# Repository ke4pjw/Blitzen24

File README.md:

# Introduction
The Blitzen 24 is a 24-port pixel controller for E1.31 (sACN) and DDP, built on the Parallax Propeller 2 (P2).

# Current State
The current release is **Blitzen 24 Edge 2.6.6 (Rocklin)**. What changed in each release is in [CHANGELOG.md](CHANGELOG.md).

Evaluation boards are available. Please contact me at ttrapp at ieee dot org if you would like to purchase one.

# Features
- **24 WS2811/WS2812 pixel outputs**, with per-output color order and brightness.
- **4 extra outputs (25–28)** for either quad DMX or a long-range pixel board.
- **E1.31 (sACN) or DDP input**, selectable per controller. Each protocol keeps its own saved layout, so you can switch back and forth without losing either one.
- **W6100 Ethernet**, with DHCP or a static address, DNS, and mDNS (`<hostname>.local`).
- **Web configuration**: network, outputs, inputs, DMX and saved configs. Live input stats, and a banner when changes haven't been saved.
- **Online upgrades** from the configs page, with a choice of the release or development channel. Each file shows download progress and is checked against its MD5.
- **OLED and rotary encoder**, with these screens: Stats, a QR code for the controller's web page, Network, Version, and Pixel Test.
- **Pixel tests**: Red, Green, Blue, White and Rainbow on each port. Start them from the OLED or the web Outputs page.

# Getting It
- **Source with Boards:** [https://griswoldfx.visualstudio.com/_git/Blitzen 24](https://griswoldfx.visualstudio.com/_git/Blitzen%2024). Each release has a branch named `Blitzen_24_Edge_<version>_<name>`.
- **Source code only in Github:** [https://github.com/ke4pjw/Blitzen24](https://github.com/ke4pjw/Blitzen24), a mirror of this repo.
- **Binary Distribution:** [https://filesgriswoldfxcom.blob.core.windows.net/firmware/Blitzen24/Blitzen 24 Edge 2.6.6 (Rocklin).zip](https://filesgriswoldfxcom.blob.core.windows.net/firmware/Blitzen24/Blitzen%2024%20Edge%202.6.6%20(Rocklin).zip). It holds everything that goes on the SD card.
- **Updates thread:** [Parallax Forums](https://forums.parallax.com/discussion/174560/blitzen-24-e1-31-pixel-light-controller-updates-thread/)

As always, you can update directly from the controller itself on the configs page.

# Repository Layout
| Path | Contents |
|------|----------|
| `Blitzen24.spin2` | Top-level firmware: web server, configuration, OLED menus |
| `W6100drv.spin2` | W6100 Ethernet driver and the fast E1.31/DDP receive cog |
| `pixeltest.spin2` | Pixel test patterns, which run in their own cog |
| `tt_rgbx_pixel.spin2`, `tt_dmx_tx.spin2` | Pixel and DMX output drivers |
| `micro_sd_fat32_fs_v180.spin2` | SD card / FAT32 filesystem driver |
| `SDCARD/` | Web pages and other files that go on the SD card |
| `Hardware/` | KiCad schematics and board layout |
| `MemoryStructure.md` | Hub memory and config layout |
| `CHANGELOG.md` | Release history |

# Known Bugs
- [#67](https://griswoldfx.visualstudio.com/Blitzen%2024/_workitems/edit/67/) In DDP mode, the pixel buffer is too small for 24 outputs × 1,020 pixels plus DMX.
- [#76](https://griswoldfx.visualstudio.com/Blitzen%2024/_workitems/edit/76/) E1.31 DMX universes copy only 510 of 512 channels.

# To Do
- [#58](https://griswoldfx.visualstudio.com/Blitzen%2024/_workitems/edit/58/) NTP client.
- [#68](https://griswoldfx.visualstudio.com/Blitzen%2024/_workitems/edit/68/), [#69](https://griswoldfx.visualstudio.com/Blitzen%2024/_workitems/edit/69/), [#70](https://griswoldfx.visualstudio.com/Blitzen%2024/_workitems/edit/70/) Configure the Blitzen 24 from xLights: discovery, a JSON config API, and an xLights driver.

# Build
Releases are built with the Spin Tools compiler (`spinc`, 0.57.3):

```
spinc -u -b -o _BOOT_P2 Blitzen24.spin2
```

`-u` removes unused methods and `-b` writes a binary. Copy the result to the SD card as `_BOOT_P2.BIX`, along with the files in `SDCARD/`.

# Credits
- **Stephen M. Moraco and Chris Gadd** wrote the `micro_sd_fat32_fs` SD card / FAT32 driver.
- **Rayman** wrote the cog-less SD card driver used in early releases.

# Contribute
If you wish to contribute, please email me. ttrapp at ieee dot org

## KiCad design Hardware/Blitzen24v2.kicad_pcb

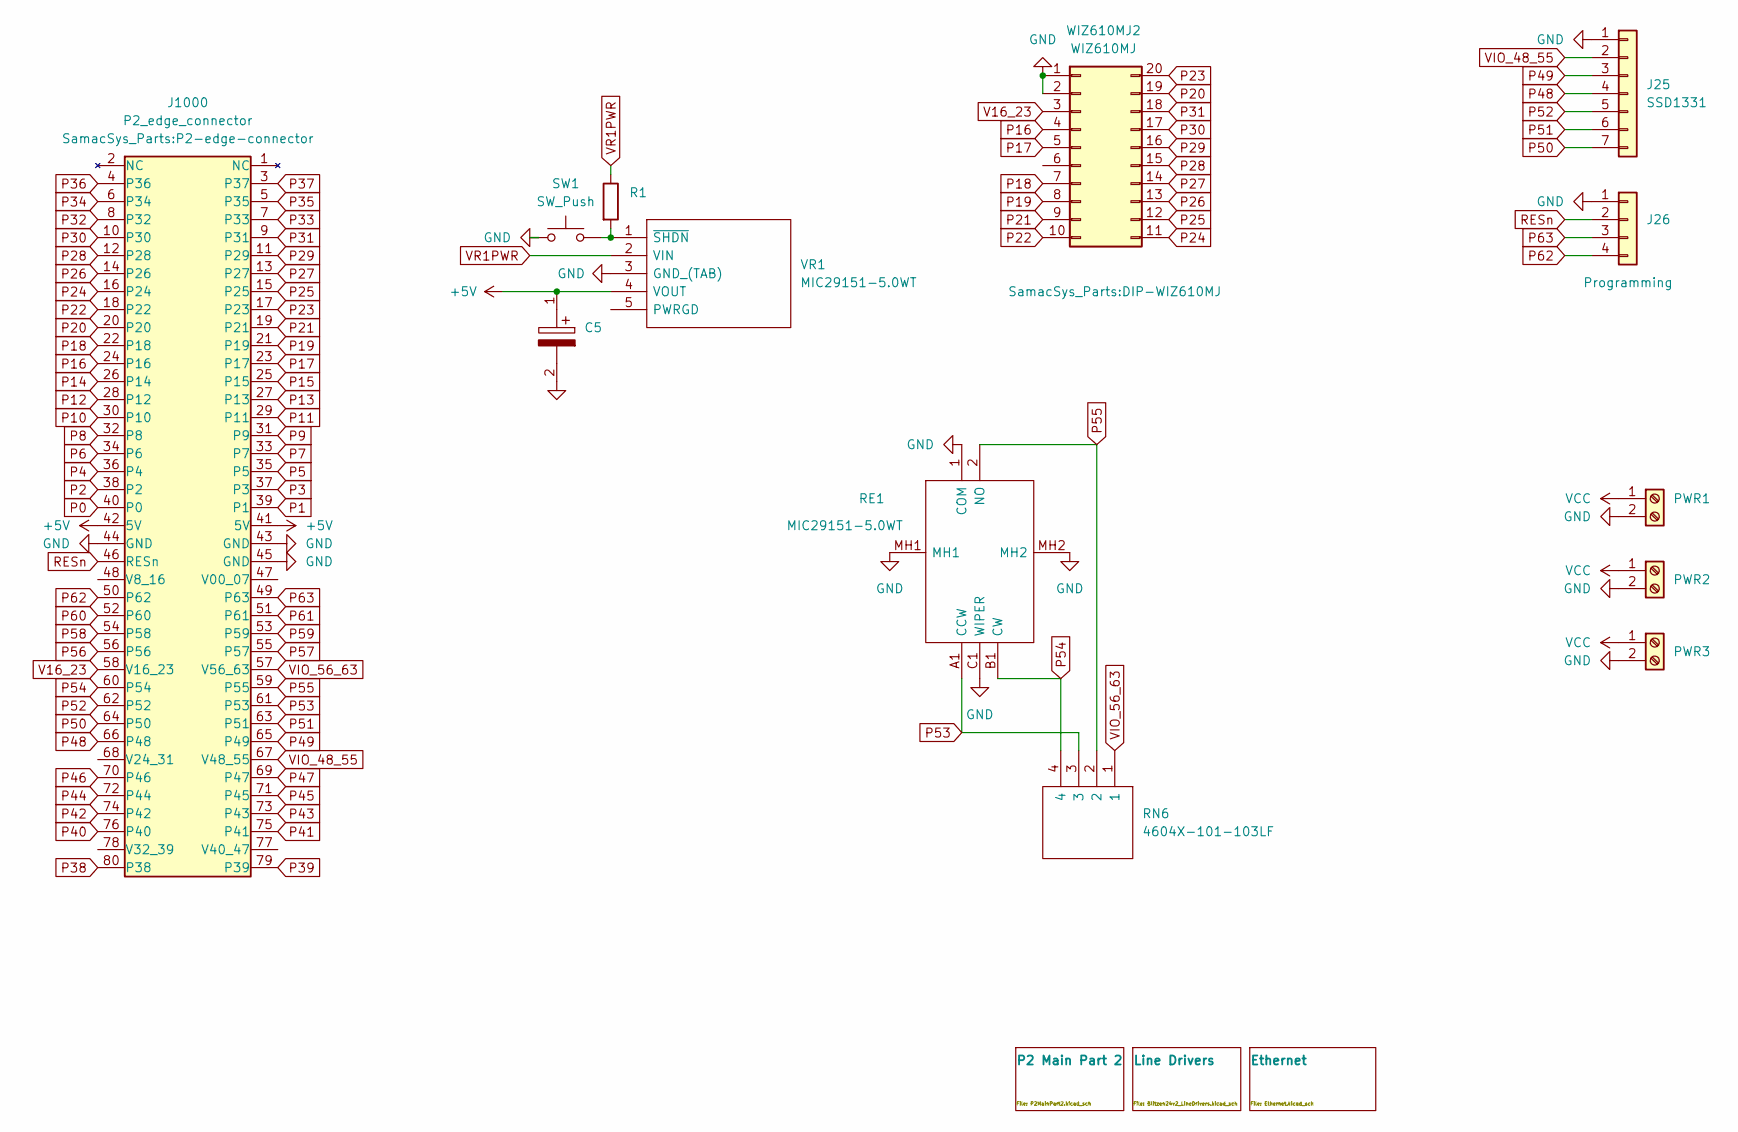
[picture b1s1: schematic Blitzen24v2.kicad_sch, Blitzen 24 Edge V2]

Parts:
C5: Mouser Part Number 80-ESS106M025AB2AA
J25: SSD1331
J26: Programming; PinHeader_1x04_P2.54mm_Vertical
J1000: P2_edge_connector; P2-edge-connector
PWR1, PWR2, PWR3: Screw_Terminal_01x02; TerminalBlock_Dinkle_DT-55-B01X-02_P10.00mm
R1: (no value)
RE1: MIC29151-5.0WT; PEC11L4015FS0020; Mouser Part Number 652-PEC11L4015FS0020
RN6: 4604X-101-103LF; 4604X101103LF; Mouser Part Number 652-4604X-1LF-10K
SW1: SW_Push
VR1: MIC29151-5.0WT; Mouser Part Number MIC29151-5.0WT
WIZ610MJ2: WIZ610MJ; DIP-WIZ610MJ

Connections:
+5V: C5.1, J1000.41 (5V), J1000.42 (5V), VR1.4 (VOUT); also elsewhere on the board
unnamed: R1.2, SW1.2, VR1.1 (~SHDN)
P0: J1000.40 (P0); also elsewhere on the board
P1: J1000.39 (P1); also elsewhere on the board
P2: J1000.38 (P2); also elsewhere on the board
P3: J1000.37 (P3); also elsewhere on the board
P4: J1000.36 (P4); also elsewhere on the board
P5: J1000.35 (P5); also elsewhere on the board
P6: J1000.34 (P6); also elsewhere on the board
P7: J1000.33 (P7); also elsewhere on the board
P8: J1000.32 (P8); also elsewhere on the board
P9: J1000.31 (P9); also elsewhere on the board
P10: J1000.30 (P10); also elsewhere on the board
P11: J1000.29 (P11); also elsewhere on the board
P12: J1000.28 (P12); also elsewhere on the board
P13: J1000.27 (P13); also elsewhere on the board
P14: J1000.26 (P14); also elsewhere on the board
P15: J1000.25 (P15); also elsewhere on the board
P16: J1000.24 (P16), WIZ610MJ2.4
P17: J1000.23 (P17), WIZ610MJ2.5
P18: J1000.22 (P18), WIZ610MJ2.7
P19: J1000.21 (P19), WIZ610MJ2.8
P20: J1000.20, WIZ610MJ2.19
P21: J1000.19 (P21), WIZ610MJ2.9
P22: J1000.18 (P22), WIZ610MJ2.10
P23: J1000.17 (P23), WIZ610MJ2.20
P24: J1000.16 (P24), WIZ610MJ2.11
P25: J1000.15 (P25), WIZ610MJ2.12
P26: J1000.14 (P26), WIZ610MJ2.13
P27: J1000.13 (P27), WIZ610MJ2.14
P28: J1000.12 (P28), WIZ610MJ2.15
P29: J1000.11 (P29), WIZ610MJ2.16
P30: J1000.10 (P30), WIZ610MJ2.17
P31: J1000.9 (P31), WIZ610MJ2.18
P32: J1000.8 (P32); also elsewhere on the board
P33: J1000.7 (P33); also elsewhere on the board
P34: J1000.6 (P34); also elsewhere on the board
P35: J1000.5 (P35); also elsewhere on the board
P36: J1000.4 (P36); also elsewhere on the board
P37: J1000.3 (P37); also elsewhere on the board
P38: J1000.80 (P38); also elsewhere on the board
P39: J1000.79 (P39); also elsewhere on the board
P40: J1000.76 (P40)
P41: J1000.75 (P41)
P42: J1000.74 (P42)
P43: J1000.73 (P43)
P44: J1000.72 (P44); also elsewhere on the board
P45: J1000.71 (P45); also elsewhere on the board
P46: J1000.70 (P46); also elsewhere on the board
P47: J1000.69 (P47); also elsewhere on the board
P48: J25.4, J1000.66 (P48)
P49: J25.3, J1000.65 (P49)
P50: J25.7, J1000.64 (P50)
P51: J25.6, J1000.63 (P51)
P52: J25.5, J1000.62 (P52)
P53: J1000.61 (P53), RE1.A1 (CCW), RN6.3
P54: J1000.60 (P54), RE1.B1 (CW), RN6.4
P55: J1000.59 (P55), RE1.2 (NO), RN6.2
P56: J1000.56
P57: J1000.55 (P57)
P58: J1000.54 (P58)
P59: J1000.53 (P59)
P60: J1000.52 (P60)
P61: J1000.51 (P61)
P62: J26.4, J1000.50 (P62)
P63: J26.3, J1000.49 (P63)
RESn: J26.2, J1000.46 (RESn)
V16_23: J1000.58 (V16_23), WIZ610MJ2.3
VCC: PWR1.1, PWR2.1, PWR3.1; also elsewhere on the board
VIO_48_55: J25.2, J1000.67 (V48_55)
VIO_56_63: J1000.57 (V56_63), RN6.1
VR1PWR: R1.1, VR1.2 (VIN); also elsewhere on the board

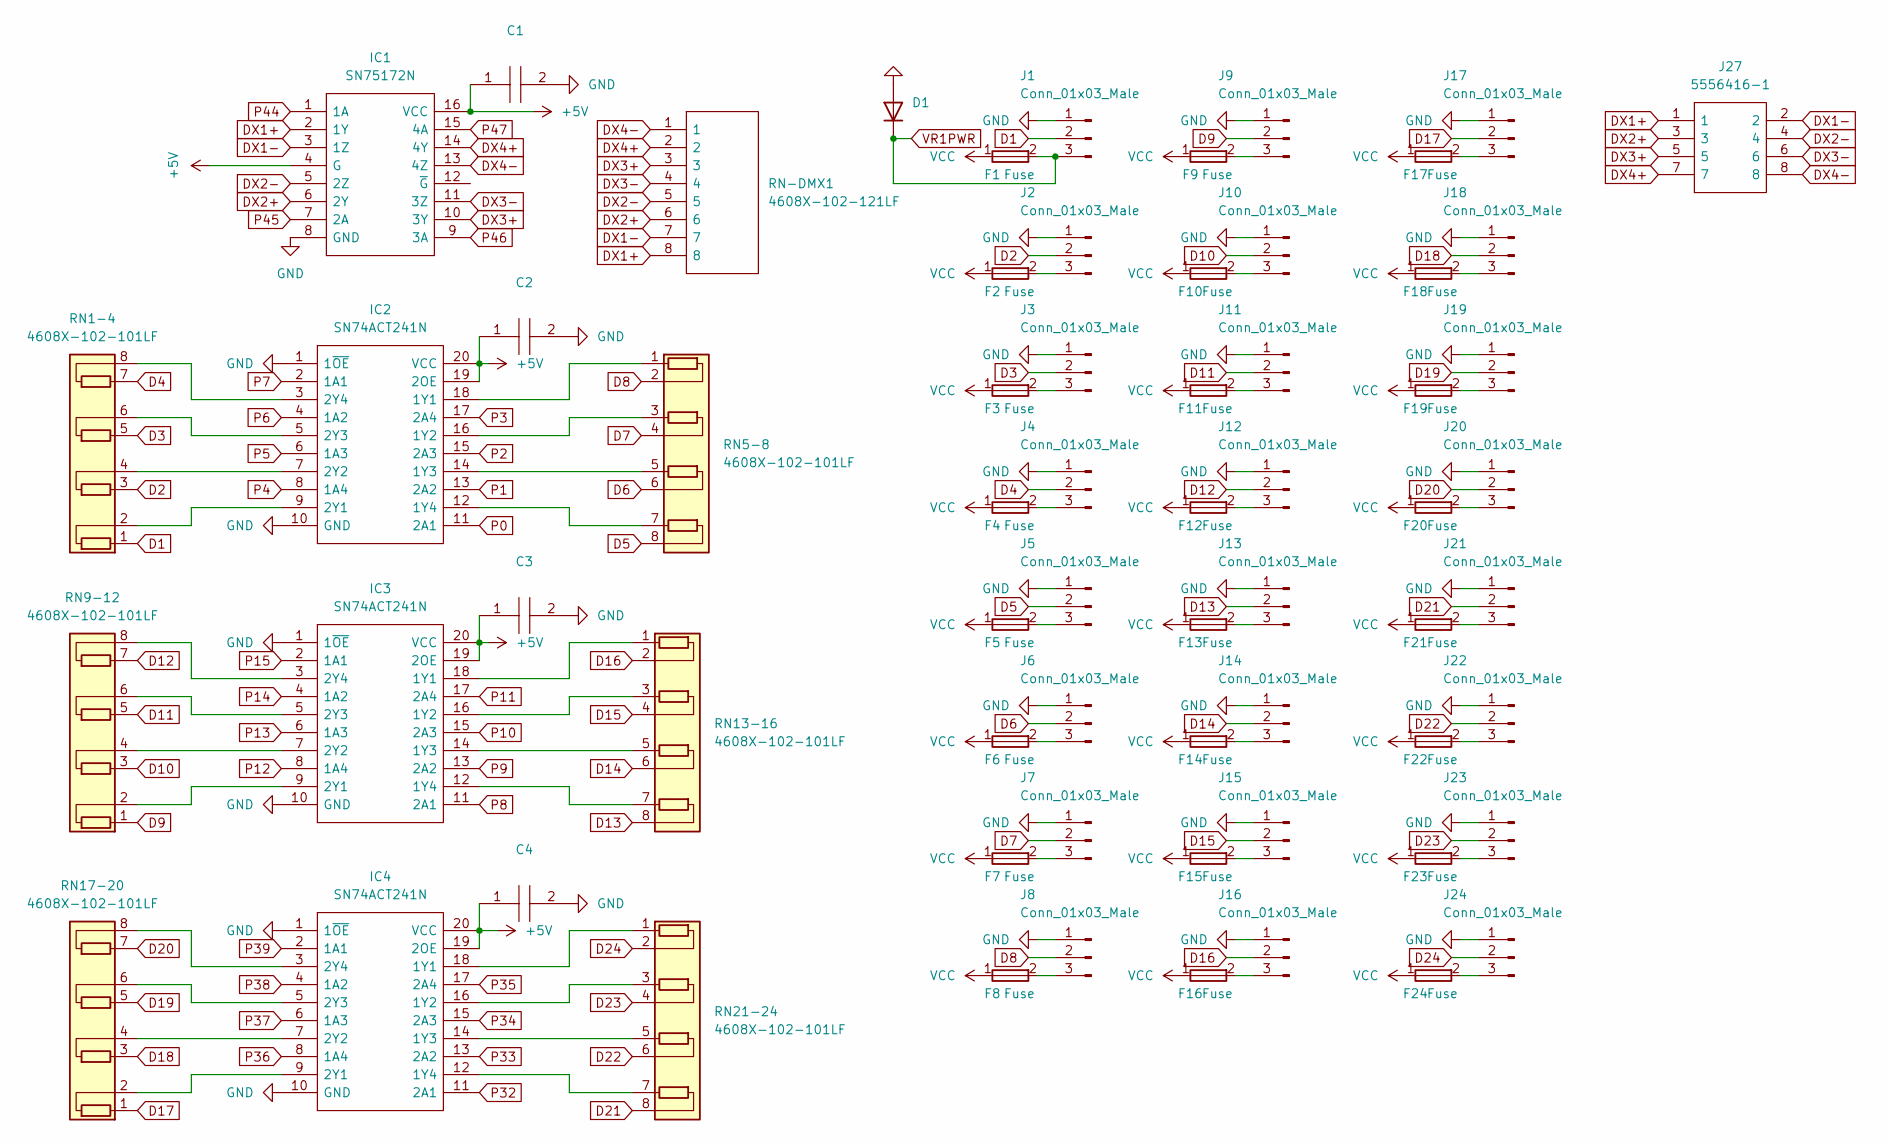
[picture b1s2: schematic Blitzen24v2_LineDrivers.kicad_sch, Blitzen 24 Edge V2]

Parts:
C1, C2, C3, C4: Mouser Part Number 80-C320C104K5R
D1: (no value)
F1, F2, F3, F4, F5, F6, F7, F8, F9, F10, F11, F12, F13, F14, F15, F16, F17, F18, F19, F20, F21, F22, F23, F24: Fuse; Fuseholder_Blade_Mini_Keystone_3568
IC1: SN75172N; DIP794W53P254L1930H508Q16N; Mouser Part Number 595-SN75172N
IC2, IC3, IC4: SN74ACT241N; DIP254P762X508-20; Mouser Part Number 595-SN74ACT241N
J1, J2, J3, J4, J5, J6, J7, J8, J9, J10, J11, J12, J13, J14, J15, J16, J17, J18, J19, J20, J21, J22, J23, J24: Conn_01x03_Male; PhoenixContact_MSTBVA_2,5_3-G-5,08_1x03_P5.08mm_Vertical
J27: 5556416-1; 55564161; Mouser Part Number 571-5556416-1
RN1-4, RN5-8, RN9-12, RN13-16, RN17-20, RN21-24: 4608X-102-101LF; R_Array_SIP8
RN-DMX1: 4608X-102-121LF; 4608X102121LF; Mouser Part Number 652-4608X-2LF-120

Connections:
+5V: C1.1, C2.1, C3.1, C4.1, IC1.4 (G), IC1.16 (VCC), IC2.19 (2OE), IC2.20 (VCC), IC3.19 (2OE), IC3.20 (VCC), IC4.19 (2OE), IC4.20 (VCC); also elsewhere on the board
D1: J1.2, RN1-4.1 (R1.1)
D2: J2.2, RN1-4.3 (R2.1)
D3: J3.2, RN1-4.5 (R3.1)
D4: J4.2, RN1-4.7 (R4.1)
D5: J5.2, RN5-8.8 (R4.2)
D6: J6.2, RN5-8.6 (R3.2)
D7: J7.2, RN5-8.4 (R2.2)
D8: J8.2, RN5-8.2 (R1.2)
D9: J9.2, RN9-12.1 (R1.1)
D10: J10.2, RN9-12.3 (R2.1)
D11: J11.2, RN9-12.5 (R3.1)
D12: J12.2, RN9-12.7 (R4.1)
D13: J13.2, RN13-16.8 (R4.2)
D14: J14.2, RN13-16.6 (R3.2)
D15: J15.2, RN13-16.4 (R2.2)
D16: J16.2, RN13-16.2 (R1.2)
D17: J17.2, RN17-20.1 (R1.1)
D18: J18.2, RN17-20.3 (R2.1)
D19: J19.2, RN17-20.5 (R3.1)
D20: J20.2, RN17-20.7 (R4.1)
D21: J21.2, RN21-24.8 (R4.2)
D22: J22.2, RN21-24.6 (R3.2)
D23: J23.2, RN21-24.4 (R2.2)
D24: J24.2, RN21-24.2 (R1.2)
DX1+: IC1.2 (1Y), J27.1, RN-DMX1.8
DX1-: IC1.3 (1Z), J27.2, RN-DMX1.7
DX2+: IC1.6 (2Y), J27.3, RN-DMX1.6
DX2-: IC1.5 (2Z), J27.4, RN-DMX1.5
DX3+: IC1.10 (3Y), J27.5, RN-DMX1.3
DX3-: IC1.11 (3Z), J27.6, RN-DMX1.4
DX4+: IC1.14 (4Y), J27.7, RN-DMX1.2
DX4-: IC1.13 (4Z), J27.8, RN-DMX1.1
unnamed: F2.2, J2.3
unnamed: F3.2, J3.3
unnamed: F4.2, J4.3
unnamed: F5.2, J5.3
unnamed: F6.2, J6.3
unnamed: F7.2, J7.3
unnamed: F8.2, J8.3
unnamed: F9.2, J9.3
unnamed: F10.2, J10.3
unnamed: F11.2, J11.3
unnamed: F12.2, J12.3
unnamed: F13.2, J13.3
unnamed: F14.2, J14.3
unnamed: F15.2, J15.3
unnamed: F16.2, J16.3
unnamed: F17.2, J17.3
unnamed: F18.2, J18.3
unnamed: F19.2, J19.3
unnamed: F20.2, J20.3
unnamed: F21.2, J21.3
unnamed: F22.2, J22.3
unnamed: F23.2, J23.3
unnamed: F24.2, J24.3
unnamed: IC2.3 (2Y4), RN1-4.8 (R4.2)
unnamed: IC2.5 (2Y3), RN1-4.6 (R3.2)
unnamed: IC2.7 (2Y2), RN1-4.4 (R2.2)
unnamed: IC2.9 (2Y1), RN1-4.2 (R1.2)
unnamed: IC2.12 (1Y4), RN5-8.7 (R4.1)
unnamed: IC2.14 (1Y3), RN5-8.5 (R3.1)
unnamed: IC2.16 (1Y2), RN5-8.3 (R2.1)
unnamed: IC2.18 (1Y1), RN5-8.1 (R1.1)
unnamed: IC3.3 (2Y4), RN9-12.8 (R4.2)
unnamed: IC3.5 (2Y3), RN9-12.6 (R3.2)
unnamed: IC3.7 (2Y2), RN9-12.4 (R2.2)
unnamed: IC3.9 (2Y1), RN9-12.2 (R1.2)
unnamed: IC3.12 (1Y4), RN13-16.7 (R4.1)
unnamed: IC3.14 (1Y3), RN13-16.5 (R3.1)
unnamed: IC3.16 (1Y2), RN13-16.3 (R2.1)
unnamed: IC3.18 (1Y1), RN13-16.1 (R1.1)
unnamed: IC4.3 (2Y4), RN17-20.8 (R4.2)
unnamed: IC4.5 (2Y3), RN17-20.6 (R3.2)
unnamed: IC4.7 (2Y2), RN17-20.4 (R2.2)
unnamed: IC4.9 (2Y1), RN17-20.2 (R1.2)
unnamed: IC4.12 (1Y4), RN21-24.7 (R4.1)
unnamed: IC4.14 (1Y3), RN21-24.5 (R3.1)
unnamed: IC4.16 (1Y2), RN21-24.3 (R2.1)
unnamed: IC4.18 (1Y1), RN21-24.1 (R1.1)
P0: IC2.11 (2A1); also elsewhere on the board
P1: IC2.13 (2A2); also elsewhere on the board
P2: IC2.15 (2A3); also elsewhere on the board
P3: IC2.17 (2A4); also elsewhere on the board
P4: IC2.8 (1A4); also elsewhere on the board
P5: IC2.6 (1A3); also elsewhere on the board
P6: IC2.4 (1A2); also elsewhere on the board
P7: IC2.2 (1A1); also elsewhere on the board
P8: IC3.11 (2A1); also elsewhere on the board
P9: IC3.13 (2A2); also elsewhere on the board
P10: IC3.15 (2A3); also elsewhere on the board
P11: IC3.17 (2A4); also elsewhere on the board
P12: IC3.8 (1A4); also elsewhere on the board
P13: IC3.6 (1A3); also elsewhere on the board
P14: IC3.4 (1A2); also elsewhere on the board
P15: IC3.2 (1A1); also elsewhere on the board
P32: IC4.11 (2A1); also elsewhere on the board
P33: IC4.13 (2A2); also elsewhere on the board
P34: IC4.15 (2A3); also elsewhere on the board
P35: IC4.17 (2A4); also elsewhere on the board
P36: IC4.8 (1A4); also elsewhere on the board
P37: IC4.6 (1A3); also elsewhere on the board
P38: IC4.4 (1A2); also elsewhere on the board
P39: IC4.2 (1A1); also elsewhere on the board
P44: IC1.1 (1A); also elsewhere on the board
P45: IC1.7 (2A); also elsewhere on the board
P46: IC1.9 (3A); also elsewhere on the board
P47: IC1.15 (4A); also elsewhere on the board
VCC: F1.1, F2.1, F3.1, F4.1, F5.1, F6.1, F7.1, F8.1, F9.1, F10.1, F11.1, F12.1, F13.1, F14.1, F15.1, F16.1, F17.1, F18.1, F19.1, F20.1, F21.1, F22.1, F23.1, F24.1; also elsewhere on the board
VR1PWR: D1.1 (K), F1.2, J1.3; also elsewhere on the board

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
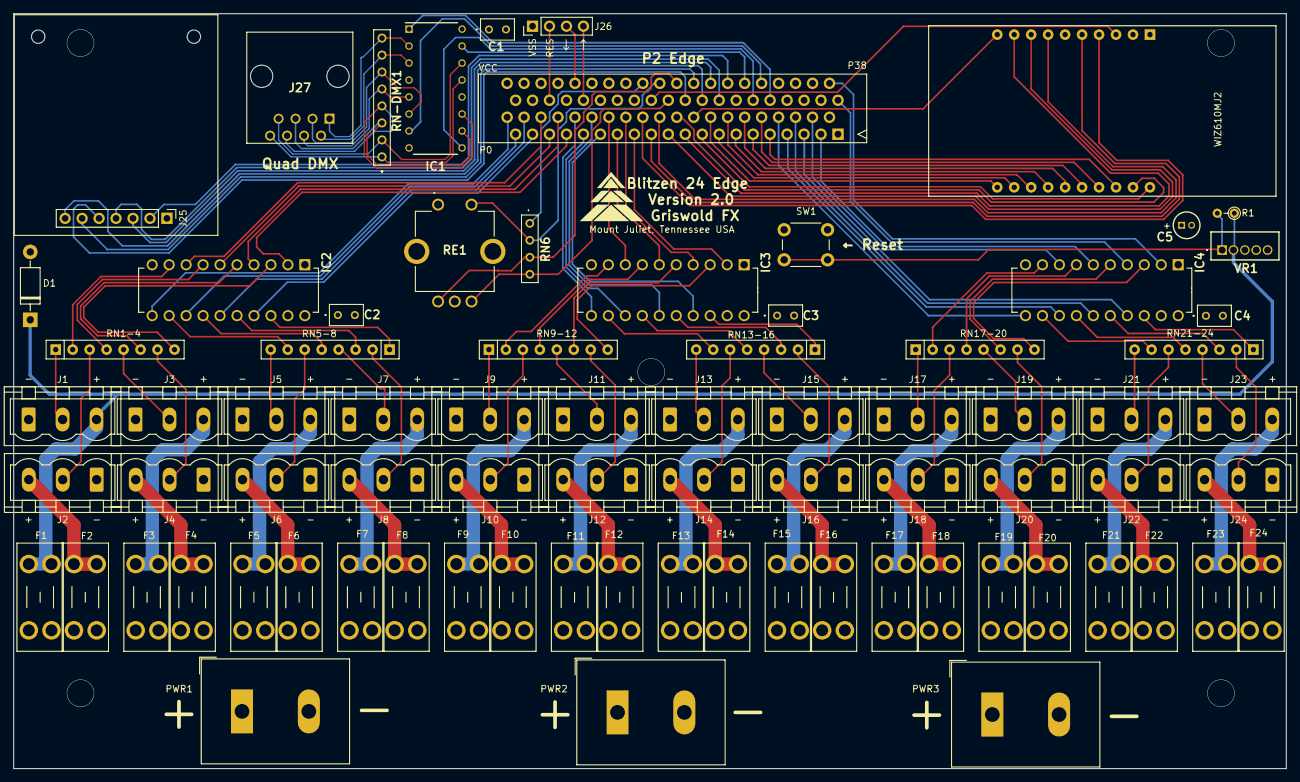
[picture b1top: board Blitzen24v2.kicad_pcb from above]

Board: 4 copper layers, 190.5 x 113.0 mm, 78 parts (0 on the bottom side), 142 nets.

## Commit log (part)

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2022-01-06 Added README.md
2022-01-06 Added 5 files to /
2022-01-09 Updated helloworld_dvi.spin2
2022-01-09 Updated 2 files under /
2022-01-14 Updated 4 files under /
2022-01-22 Updated 3 files under /
2022-03-02 Updated 3 files under / Start of dynamic pixel config.
2022-03-03 Updated 2 files under /
    Multi Universes per pin works
2022-03-04 Updated jm_rgbx_pixel.spin2
2022-03-06 Multiple Universes now mapped to multiple pins. Single cog running 8 WS2812b pins
2022-03-07 Corrected bug with E1.31 array. Added W6100 interrupt for socket 3. Fixed bug where socket was not being cleared correctly.
2022-03-07 Updated jm_rgbx_pixel.spin2
    Fixed bug where Red was one pixel off, causing color tearing.
2022-03-10 Best Effort working
2022-03-12 added youtube video Updated README.md
2022-03-15 Fixed bug in pin output configuration for 2nd ws2812 output. Added outputs in config for more E1.31 universes.
2022-03-22 Updated README.md New video URL
2022-03-24 Deleted Overview
2022-03-31 Per Jon's request Deleted jm_rgbx_pixel.spin2
2022-03-31 Updated 2 files under /
    Updated comments to reflect this is not Jon's driver and changed filename per Jon's request.
2022-04-06 Updated 2 files under / SD card driver, webserver, and resource locking added.
2022-04-06 Added 5 files to / Additional files to support new features.
2022-04-06 Added 3 files to /SDCARD
2022-04-07 Updated README.md Updated ToDo list.
2022-04-08 Updated W6100drv.spin2 Added .75ms delay for 10mbps TCP bug
2022-04-11 Bootstrap config on SD card. Load config from SD card. Enable DHCP on first boot. Create unique MAC on first time boot.
2022-04-12 Updated 8 files under /SDCARD A website is born.
2022-04-12 Updated test.spin2 Website created. net.js populates net.htm form
2022-04-13 Updated test.spin2 net.htm URL now processes posts.
2022-04-15 Updated 6 files under /SDCARD Created additional config files. work focused on e131.htm
2022-04-15 Updated 5 files under /SDCARD
2022-04-16 Updated e131.htm
2022-04-16 Updated test.spin2
2022-04-18 Updated test.spin2 E1.31 configs can be modified in memory.
2022-04-18 Updated test.spin2 Removed debuginfo and waits
2022-04-19 Updated 2 files under / Added restart of pixel driver and E131 receiver cogs when E131 config updated.
2022-04-20 Updated 2 files under /SDCARD Added save config, download running config, and download boot config in configs.htm
2022-04-20 Updated test.spin2 Updated configs.htm processing.
2022-04-22 Updated test.spin2
    Config File Upload almost working
2022-04-23 Updated test.spin2
    Uploads appear to be working. Needs testing.
2022-04-23 Updated test.spin2 Fixed uploads for MS Edge.
2022-04-23 Updated test.spin2 Fixed bug with MIME type for downloading boot config.
2022-04-23 Updated test.spin2 Upload of config files working.
2022-04-25 Updated 3 files under /SDCARD Updated E131 config page to validate data.
2022-04-25 Updated test.spin2 Updated E131 config pages
2022-04-26 Updated net.htm
2022-04-27 Updated 3 files under / Added individual RBGswaps in the pixel driver.
    Minor change in W6100 driver.
2022-04-27 Updated 3 files under / More bugs found and squashed.
    Some still open. See related work item.
2022-04-28 Updated outputs.htm
2022-04-28 Deleted BLITZEN.CFG
    Config Memory Changed
2022-04-30 Updated 2 files under / 10Mbs is default setting.
2022-06-10 Work in progress for Blitzen 24 Edge
2022-07-07 Updated 6 files under / OLED Added
2022-07-08 Updated 2 files under / Fixed counter issue.
2022-07-10 Updated 2 files under / Added counters to homepage
2022-07-10 Updated index.htm Added counters to homepage
2022-07-29 Updated Blitzen_24_Edge.rrb
2022-08-05 Updated 2 files under /Hardware
2022-08-09 Prototype Board Order
2022-08-22 Updated test.spin2 Fixed outputs 13-24 Moved start and stop of pixeloutput cogs to methods.
2022-08-25 Migrated to a cog-less SD card driver. Thank you Rayman!
2022-08-26 Added EP00026917.zip to /Hardware
    Gerber Files
2022-10-07 Updated test.spin2
    Updated Counters on OLED and Webpage
2022-10-19 Updated test.spin2
    Added Master Dimmer.
    Added pixel cog restart when outputs updated.
2022-10-20 Updated 2 files under / Added Brightness to the pixel driver
2022-10-20 Updated outputs.htm to include brightness control
2022-10-27 Deleted outputs.htm
2022-11-06 May not be working
2022-11-06 Updated W6100drv.spin2 Working with bypass cap on CS line
2022-11-06 Updated W6100drv.spin2
2022-11-07 Updated W6100drv.spin2 .1uF cap on CS line and this code works good enough. No more glitching on pixels.
2022-11-08 Updated W6100drv.spin2 Seems to works best with webserver and no glitches
2022-12-11 Updated 3 files under / * Only starts pixel cogs where pixelcount is > 1 * More debug items turned on
2022-12-11 Updated 3 files under / Updated W6100 driver so that all cogs drive WRn,RDn,A0,A1, and CS all the time. This required the signals to be inverted.
    Reduced drive to pins 5 - 8 in pixel driver.
    Solved 99% of glitching.
2022-12-17 Updated 2 files under / Fixed scheduling issue with watchdog and httpd cogs. Added method to test.spin2 to enumerate pixelconfig to determine pixel count. Untested and unused.
2022-12-20 Deleted test.spin2 File is now Blitzen24.spin2
2022-12-20 Added Blitzen24.spin2 to / Previous Versions would set pixel string length based on the first pin of the pingroup. Now pixel string length for the pingroup is based on the highest pixel count in the 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
2022-12-20 Updated Blitzen24.spin2
    Forgot to add the new changes to the pixel startup for pingroup 9 and 17
2022-12-21 Updated Blitzen24.spin2
    Added many comments.
    Fixed system locking up if Universe updated/removed
2022-12-30 Updated Blitzen24.spin2
    Moved all OLED display updates to the watchdog cog and moved the startup of that cog before DHCP configuration.
2022-12-31 Updated Blitzen24.spin2 Added better wait time in the watchdog cog.
2023-01-01 Added dmx.htm to /SDCARD
2023-01-01 Updated 2 files under /
    Quad DMX output is working.
2023-01-02 Updated Blitzen24.spin2 Converted all video out to debug info.
2023-01-02 Updated W6100drv.spin2
    Found the video driver referenced in here and removed it.
2023-01-02 Updated 2 files under /SDCARD
2023-01-02 Updated 2 files under / Ethernet Speed and Duplex added. DNS and DNS via DHCP added.
2023-01-02 Updated 2 files under /
    Some more debug cleanup. Added string termination to the webserver's received data so that it displays properly in the debug. Does not seem to affect anything.
2023-01-02 Updated tt_dmx_tx.spin2 Was missing an extra long to copy into cog ram. Baud ticks was missing. Updated and fixed.
2023-01-03 Updated tt_dmx_tx.spin2
    Corrected the start code to be NULL.
2023-01-04 Updated Blitzen24.spin2 Added test code for DNS resolver.
2023-01-05 Updated Blitzen24.spin2
    DNS resolver works for A records and CNAMES.
2023-01-06 Updated configs.htm
2023-01-06 Updated 2 files under /
    Outbound TCP is working
2023-01-09 Added upgrade.htm to /SDCARD
2023-01-10 Updated Blitzen24.spin2 Can't get file enumeration to work with the root directory on the copydirectory object.
2023-01-10 Updated 2 files under /
    First working copy of over the air updates.
2023-01-11 Updated Blitzen24.spin2
    Blitzen 24 Edge 1.0 PR4
2023-01-13 Updated Blitzen24.spin2
2023-01-20 Added 2 files to /SDCARD
2023-01-21 Updated reboot.htm Reboot page had the wrong heading.
2023-01-21 Updated 5 files under / This will be the 1.1 release
2023-01-21 Updated Blitzen24.spin2 Fixed last moment bug in server response codes showing as MD5 mismatches.
2023-01-21 Fixed last moment bug in http response codes during upgrades.
2023-01-22 Updated Blitzen24.spin2
    Added retries to updates and fixed some problems with properly disconnecting outbound connections.
2023-01-22 Updated upgrade.htm Minor change to preload reboot image.
2023-02-01 Added dmx.htm to /
2023-02-01 Deleted dmx.htm
2023-02-01 Updated dmx.htm
2023-02-02 Additional duplicate universe checking added to the current output that is being updated.
2023-02-04 Added GFX.raw to /SDCARD Bootup Screen
2023-02-04 Updated Blitzen24.spin2 Added bootup logo when waiting for the network to settle.
2023-02-07 Revert "Updated 3 files under /"
2024-09-21 Updated 5 files under / This is the V2.0 Board files
2024-09-21 Updated 2 files under / Fixed quadrature Encoder. Added pushbutton wakeup. Added version menu.
2024-09-22 Updated Blitzen24.spin2
    Fixed bug with pixel tests when not in the stats menu.
2024-09-23 Updated 2 files under / Added uptime to menu.
2025-02-15 Added MemoryStructure.md Keeping track of this structure to add long range boards. Unfortunately I did not allow enough ports in the PIXELCONFIG structure. I need to decide if I want to lose compatib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
2025-02-20 Updated 3 files under /SDCARD
2025-02-24 Updated Blitzen24.spin2 Fixed some code that should have been commented out.
2026-01-27 Updated 2 files under /SDCARD Also Added Hostname
2026-01-27 Updated Blitzen24.spin2 Also Added hostname
2026-03-13 Deleted FAT32.spin2
2026-03-13 Deleted sdspi_bashed2.spin2
2026-03-13 Deleted sdspi_with_audio.spin2
2026-03-13 Updated 3 files under / Changed FS object over to micro_sd_fat32_fs.spin2
2026-03-27 Updated 2 files under / Added defrag.
2026-04-16 Deleted Blitzen_23_Edge.sch
2026-04-16 Deleted Blitzen_24_Edge.rrb
2026-04-16 Deleted EP00026917.zip
2026-04-16 Added 12 files to /Hardware
2026-04-30 Set up CI with Azure Pipelines
    [skip ci]
